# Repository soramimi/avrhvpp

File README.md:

# avrhvpp

ATmega32U2 で動作する、AVR マイコン用の +12V 高電圧パラレルプログラマ（HVPP）です。
通常は STK500 互換の ISP プログラマとして動作し、専用コマンドを送ると高電圧パラレルプログラミングモード（AVRHVPP モード）に切り替わります。

ヒューズ設定の誤りで ISP が使えなくなったチップ（SPIEN 無効、DWEN 有効など）の読み出しと復旧を主な目的としています。

ホストツールは、対応する7チップでシグネチャ、ヒューズ／ロック、Flashページ／Intel HEXの読み書きとチップ消去に対応します。ATmegaの5チップはHVPP／AVRISPに、ATtiny2313／ATtiny13AはAVRISPのみに対応します。2026-11-10、ユーザーがATmegaの5チップについてHVPP／AVRISPの全対応コマンドを実機確認し、問題がないことを報告しました。当時のAVRISP拡張の実装計画は全工程完了・クローズしています。今回追加したATtinyの2チップは実機未確認です。ホストツールとHVPPのEEPROM読み書きは未実装です。

## 対応ターゲット

Flashのページ／Intel HEX操作は`--target <name>`で次のターゲットを指定します。

| ターゲット | シグネチャ | Flash容量 | ページサイズ | ページ数 | プログラマ種別 |
|---|---|---|---|---|---|
| `atmega8` | `1E 93 07` | 8 KiB | 64バイト | 128 | HVPP／AVRISP |
| `atmega48` | `1E 92 05` | 4 KiB | 64バイト | 64 | HVPP／AVRISP |
| `atmega88` | `1E 93 0A` | 8 KiB | 64バイト | 128 | HVPP／AVRISP |
| `atmega168` | `1E 94 06` | 16 KiB | 128バイト | 128 | HVPP／AVRISP |
| `atmega328p` | `1E 95 0F` | 32 KiB | 128バイト | 256 | HVPP／AVRISP |
| `attiny2313` | `1E 91 0A` | 2 KiB | 32バイト | 64 | AVRISPのみ |
| `attiny13a` | `1E 90 07` | 1 KiB | 32バイト | 32 | AVRISPのみ |

ターゲット固有値とワードアドレス計算は`common/target.h`に集約しています。ATmega8は[データシート](https://ww1.microchip.com/downloads/en/DeviceDoc/Atmel-2486-8-bit-AVR-microcontroller-ATmega8_L_datasheet.pdf)のParallel Programming（218～225ページ）でピン配置、モード移行、アドレス指定、ページロード／書き込み手順を確認しました。

ATmega48／88／168は[データシート](https://ww1.microchip.com/downloads/en/DeviceDoc/Atmel-2545-8-bit-AVR-Microcontroller-ATmega48-88-168_Datasheet.pdf)の32.2～32.7節で拡張ヒューズ、シグネチャ、ページ構成、HVPPピン配置、モード移行、Flashのアドレス指定とページロード／書き込みを確認し、定義を追加しました。3種類とも`--query`で拡張ヒューズを表示します。P／PA／PBなど異なるシグネチャの品種は今回追加していません。3種類ともHVPP／AVRISPの全対応コマンドをユーザーが実機確認済みです。データシートのモード移行手順にはVCCの切り替えが含まれますが、常時給電の現回路での動作確認で問題は報告されていません。ファームウェアのモード移行処理は変更していません。

ATtiny2313は[データシート](https://ww1.microchip.com/downloads/en/DeviceDoc/Atmel-2543-AVR-ATtiny2313_Datasheet.pdf)の158～160、172～175ページ、ATtiny13Aは[データシート](https://ww1.microchip.com/downloads/aemDocuments/documents/MCU08/ProductDocuments/DataSheets/ATtiny13A-Data-Sheet-DS40002307A.pdf)の17.1～17.6節で、シグネチャ、Flashページ構成、ヒューズ／ロック、ISP命令と完了待ちを確認しました。STK500の標準設定値は[avrdude v8.1のターゲット定義](https://github.com/avrdudes/avrdude/blob/v8.1/src/avrdude.conf.in)も参照しています。両チップとも書き込み・消去後はRDY/BSYをポーリングします。ATtiny2313には拡張ヒューズがありますが、ATtiny13Aにはありません。ATtiny13Aのhigh fuseは下位5ビットが有効で、SPIENはlow fuseのbit 7です。両チップのロックビットは下位2ビットです。

ATtinyの2チップは`--device avrisp`を指定し、ISPヘッダJ2へ接続して使用します。本プロジェクトではHVPPに対応せず、既定のHVPPまたは`--device hvpp`と組み合わせたターゲット指定は、読み出しを含む全操作で接続前に拒否します。ターゲット未指定のHVPPの`--query`で検出した場合も、ヒューズ／ロックは読み出さず失敗します。ATtiny2313Aなど他品種の定義は追加していません。

未知の名前と複数回のターゲット指定は接続前に拒否します。Flash操作では指定が必須です。ヒューズなどの操作での指定必須化、指定ターゲットとのシグネチャ照合、既存HVPP操作へのヒューズ等の対応機能による実行可否判定は未実装です。

2026-11-10、既存5チップ（ATmega8／48／88／168／328P）、HVPP／AVRISP、全対応コマンドで問題がないことをユーザーが確認しました。自動テストと実機確認を含む当時のステップ1～8は完了し、実装計画をクローズしました。

最終ビルド記録はFlash 9422 / 32768バイト（28.8%）、RAM 676 / 1024バイト（66.0%）です。

## ディレクトリ構成

| パス | 内容 |
|---|---|
| `firmware-atmega32u2/` | プログラマ本体（ATmega32U2）のファームウェア |
| `app/` | ホスト用コマンドラインツール（`avrhvpp`） |
| `common/` | 共有するコマンド／プロトコル定義と、ホスト用のターゲット定義 |
| `pcb/` | KiCad の回路図・基板データ、ガーバー |

## ハードウェア

- MCU: ATmega32U2（16MHz クリスタル、USB CDC で接続）
- ターゲット: 28 ピン ZIF ソケット（ATmega328P／ATmega8で読み書き確認済み）
- +12V: MT3608 昇圧モジュール（J4 経由）→ 12V レギュレータ（U3）で生成し、PC817 フォトカプラでターゲットの RESET に印加します。印加しないときは R6 により RESET が GND に落ちるので、ソケットのチップはリセット状態で停止しています。
- ターゲットの VCC は常時供給されます（VCC の切り替え回路はありません）。

### ピン割り当て（ATmega32U2 ↔ ターゲット）

| ATmega32U2 | 信号 | ターゲット（ATmega328P DIP28） |
|---|---|---|
| PD0–PD7 | DATA0–7 | PB0–PB5（14–19 番）、PC0–PC1（23、24 番） |
| PB3 | RDY/BSY | PD1（3 番） |
| PB4 | PAGEL | PD7（13 番） |
| PB5 | XA1 | PD6（12 番） |
| PB6 | XA0 | PD5（11 番） |
| PB7 | XTAL1 | XTAL1（9 番） |
| PC2 | +12V 制御（PC817） | RESET（1 番） |
| PC4 | OE | PD2（4 番） |
| PC5 | WR | PD3（5 番） |
| PC6 | BS1 | PD4（6 番） |
| PC7 | BS2 | PC2（25 番） |

STK500 モードでは PB0（RST）、PB1（SCK）、PB2（MOSI）、PB3（MISO）を ISP 用に使い、6 ピンヘッダ J2 に出しています。PB3 は RDY/BSY と共用です。
J3 をショートすると J2 の RST が ATmega32U2 自身の RESET につながり、外部のプログラマから ATmega32U2 にファームウェアを書き込めます。

## ビルドと書き込み

### ファームウェア

avr-gcc と avrdude が必要です。

```sh
cd firmware-atmega32u2
make            # avrhvpp.hex を生成
make write      # 外部 ISP プログラマ（avrisp, /dev/ttyACM0）で書き込み（ヒューズ hfuse=0xD9, lfuse=0x5E も設定）
make readfuse   # ATmega32U2 のヒューズを読み出し
```

`Makefile` はコンパイル時に `.d` ファイルを生成し、ヘッダの依存関係を追跡します。

### ホストツール

C++17 のコンパイラが必要です。Qt Creator で `app/avrisp.pro` を開くか、次のようにビルドします。

```sh
cd app
g++ -std=c++17 -Wall -Wextra main.cpp serial.cpp -o avrhvpp
```

## 自動確認と確認状況

リポジトリのルートで実行します。実機へのアクセスやavrdudeの起動は行いません。

```sh
make -C tests
```

| テスト | 検証する内容 |
|---|---|
| `tests/protocol.cpp` | 実際のホスト処理とHVPPファームウェアを模擬GPIOで接続。AVRISPはシリアル・ターゲットモデルで分割送受信、7チップの読み書き・消去・HEX、事前確認、異常応答・期限切れ・終了処理を検証。ATtinyのHVPP指定拒否、ヒューズ構成とSPIEN保護も確認 |
| `tests/stk500.cpp` | 変更していないファームウェアの`main.cpp`を使用し、USBバッファ・STK500解析・SPI処理を検証。7チップの標準設定、シグネチャ、ヒューズ／ロック、ページ転送、消去後再初期化、終了、モード切り替えを確認 |

STK500の要求列は[avrdude v8.1の実装](https://github.com/avrdudes/avrdude/blob/v8.1/src/stk500.c)とAVR061に基づいて構成した固定データです。実機で採取した通信ログではありません。USB入力を1／7／16バイトに分割し、ページ境界・最終ページ、最大256バイト転送とデータ中の制御値も確認します。

異常系テストでは想定したエラーメッセージを出力します。終了コード0と、`Protocol integration and boundary tests passed without hardware.`および`STK500v1 firmware compatibility fixtures passed without hardware.`の合格表示を確認してください。

サニタイザ付きで両テストを実行する場合は次を使います（LeakSanitizerは実行環境の制約により無効化）。

```sh
ASAN_OPTIONS=detect_leaks=0 make -C tests CXXFLAGS='-std=c++17 -Wall -Wextra -fsanitize=address,undefined -fno-omit-frame-pointer' TEST_BINARY=/tmp/avrhvpp-sanitized
```

AVRISP拡張によるファームウェアの動作変更はありません（Copyright表記のみ2026へ更新）。ATtinyの追加でもファームウェアは変更していません。自動確認では実際のUSBコントローラ、SPIの電気信号、実時間のタイミング、実際のavrdudeプロセスと実機の組み合わせまでは検証しません。実機確認は別途ユーザーが実施し、2026-11-10にATmegaの5チップ・HVPP／AVRISP・全対応コマンドで問題なしと報告しました。ATtiny2313／ATtiny13Aの実機確認は未実施です。

## 使い方

### STK500 互換モード（ISP）

電源投入時はこのモードです。ArduinoISP 由来の STK500v1 実装なので、avrdude からは `avrisp` として使えます。

```sh
avrdude -c avrisp -P /dev/ttyACM0 -b 19200 -p atmega328p -U flash:w:foo.hex
```

### ホストツール（HVPP／AVRISP）

ホストのプログラマ種別は`-d <device>` / `--device <device>`で指定します。既定の`hvpp`では従来のHVPP操作を使用できます。`avrisp`ではSTK500v1経由のシグネチャ、`--query`（`-q`）、ヒューズ／ロック、Flashページ／HEXの読み出しに対応します。ヒューズ／ロック書き込み、チップ消去、Flashページ書き込みにも対応します。AVRISPの`--write-hex`にも対応します。

```sh
./avrhvpp --port /dev/ttyACM0 --device avrisp --read-signature
./avrhvpp --port /dev/ttyACM0 --device avrisp -q
./avrhvpp --port /dev/ttyACM0 --device avrisp -rfl -rfh -rl
./avrhvpp --port /dev/ttyACM0 --device avrisp --target atmega328p --read-page 255 page.bin
./avrhvpp --port /dev/ttyACM0 --device avrisp --target atmega8 --read-hex flash.hex
./avrhvpp --port /dev/ttyACM0 --device avrisp --target atmega328p --write-hex firmware.hex
./avrhvpp --port /dev/ttyACM0 --device avrisp --target atmega328p --write-hex firmware.hex --no-chip-erase
./avrhvpp --port /dev/ttyACM0 --device avrisp --target attiny2313 -q
./avrhvpp --port /dev/ttyACM0 --device avrisp --target attiny13a --write-hex firmware.hex
```

AVRISPの送受信は分割されても全バイトが揃うまで処理し、応答の`STK_INSYNC`と`STK_OK`を検証します。同期は最大3回試し、各応答は1秒の期限で読み取ります。複数の読み出し操作は1回のプログラミングセッションで順に処理し、全読み取りと終了処理が成功してから成功結果を表示します。`--target`を指定した場合は、ターゲット定義から生成した標準のSET_DEVICE／SET_DEVICE_EXT設定をモード移行前に送信します。指定ターゲットとのシグネチャ自動照合は行いません。

`--query`は`--target`不要で、HVPPと同じ形式でチップ情報と対応するヒューズ／ロックを表示します。単独のヒューズ／ロック読み出しでは、指定ターゲット、またはシグネチャから検索した定義を使います。未知のシグネチャでは検索に失敗し、ヒューズ／ロックを読みません。ATmega8の拡張ヒューズは`--query`で省略し、単独の`-rfe`指定は拒否します。ページ／HEX読み出しは`--target`必須です。ページ全体／Flash全体の読み出し成功後にファイルを保存するため、通信途中の失敗では対象ファイルを作成・上書きしません。保存後に終了処理が失敗した場合は、保存済みファイルを残して非0で終了します。

AVRISPの`--write-page`は`--target`必須で、入力サイズとページ番号を接続前に検証します。内容が一致するページは書き込みを省略し、全バイトFFのページだけを書き込み、それ以外は消去せず拒否します。書き込み後はページ全体を読み戻して照合します。`--chip-erase`は完了待ち後にロックビット解除と全FlashのFFを確認します。EEPROMの消去・保持はターゲットのEESAVE設定に従います。

ページ／HEXのファイル処理とページ走査はHVPP／AVRISPで共通です。`--write-hex`は接続前にHEX全体を検証し、既定でチップを消去してから、HEXで指定されたページだけを書き込みます。`--no-chip-erase`では全対象ページが空か一致することを先に確認し、競合や読み出し失敗があれば1ページも書きません。一致ページは省略し、HEXに含まれないページは書き込みません。`--device`、`--target`、`--no-chip-erase`の記述位置によらず、操作は左から順に実行します。

ヒューズ／ロック書き込みと消去では、指定ターゲットがなければ、最初に独立した読み出しセッションでシグネチャから定義を検索します。定義を確定して標準設定を送り直してから、指定操作を順に実行します。未知のシグネチャには書き込み・消去を送りません。ATmega8は書き込み後10 ms／消去後20 ms待機し、他6チップはRDY/BSYのbit 0を最大100 msポーリングします。STK500のACKだけでは成功と判定しません。

予約ビットは1へ正規化し、有効ビットで読み戻しを照合します。SPIENの変更と、消去なしのロックビット0→1変更は拒否します。ATmega8／ATtiny13Aの拡張ヒューズ読み書きも拒否します。失敗後の操作は停止し、非0で終了します。それまでに照合済みの書き込み・消去は失敗時も表示し、取り消しません。失敗した要求は再送しません。単独ページ書き込みで自動消去は行いません。

モード移行を試みた後は、要求の境界を確認できる場合に終了コマンドを送り、終了処理は一度だけ再試行します。2バイトの同期・モード開始・シグネチャ読出し・終了要求は、送信済み位置から残りを補って終了を試みます。可変長要求の途中送信失敗では、残りを埋めたり要求を再送したりせず接続を閉じ、プログラミングモードの解除を確認できないことを報告します。

不明なプログラマ種別、種別の重複指定、AVRISPで未対応の操作は接続前に拒否します。`--device`の位置にかかわらず、全操作の検証が済んでから接続します。

```sh
./avrhvpp -p /dev/ttyACM0 --read-signature      # シグネチャを読み出し
./avrhvpp -p /dev/ttyACM0 --query              # チップを検出し、対応するヒューズとロックビットを表示
./avrhvpp -p /dev/ttyACM0 --read-fuse-low       # low fuse を読み出し
./avrhvpp -p /dev/ttyACM0 --read-fuse-high      # high fuse を読み出し
./avrhvpp -p /dev/ttyACM0 --read-fuse-extended  # extended fuse を読み出し
./avrhvpp -p /dev/ttyACM0 --read-lock           # ロックビットを読み出し
./avrhvpp -p /dev/ttyACM0 --target atmega328p --read-page 0 page.bin # Flashのページ0を128バイトのファイルへ保存
./avrhvpp -p /dev/ttyACM0 --target atmega328p --read-hex flash.hex   # Flash全体をIntel HEXへ保存
./avrhvpp -p /dev/ttyACM0 --target atmega328p --write-page 0 page.bin # 128バイトのファイルをFlashのページ0へ書き込む
./avrhvpp -p /dev/ttyACM0 --target atmega328p --write-hex example/blink.hex # Intel HEXをFlashへ書き込む
./avrhvpp -p /dev/ttyACM0 --target atmega328p --no-chip-erase --write-hex example/blink.hex # チップ消去せずに書き込む
./avrhvpp -p /dev/ttyACM0 --write-fuse-low 0x62 # low fuse に 0x62 を書き込む
./avrhvpp -p /dev/ttyACM0 --write-lock 0xFC     # ロックビットに 0xFC を書き込む
./avrhvpp -p /dev/ttyACM0 --chip-erase          # Flash、EEPROM、ロックビットを消去
./avrhvpp -p /dev/ttyACM0 --dump-buffer         # 共有バッファを16進ダンプする（デバッグ用）
```

ヒューズ値を誤るとISPでアクセスできなくなることがあります。ロックビットは0のビットがプログラムされ、1へ戻すにはチップ消去が必要です。チップ消去はFlashとロックビットに加え、EESAVE fuseがプログラムされていなければEEPROMも消去します。Flashページ書き込みは、ページが消去済み（全バイト `0xFF`）か、すでに入力データと完全一致する場合だけ成功します。`--write-hex` は既定で書き込み前にチップ消去します。消去したくない場合は `--no-chip-erase` を指定してください。書き込む値と対象チップを確認してから実行してください。

シグネチャの出力例:

```
0x1e, 0x95, 0x0f
```

`--query`（省略形`-q`）は`--target`を指定せずに実行できます。シグネチャ3バイトから定義済みターゲットを検索し、チップ名、ページサイズ、総ページ数、Flashサイズと、対応するヒューズ／ロックビットを表示します。ATmega328Pの場合の出力例:

```text
signature: 0x1e, 0x95, 0x0f
chip: ATmega328P
page size: 128 bytes
page count: 256
flash size: 32768 bytes
fuse lo: 0x62
fuse hi: 0xd9
fuse ex: 0xff
lock bits: 0xfc
```

上記のヒューズ／ロック値は例です。ATmega8では拡張ヒューズを読み出さず、その行も表示しません。未定義のシグネチャでは`chip: unknown`を表示し、ヒューズ／ロックを読まず非0で終了します。取得失敗や異常応答でも後続操作を停止します。検出結果は後続のFlash操作の`--target`指定を変更しません。

オプション:

| オプション | 内容 |
|---|---|
| `-p <port>`, `--port <port>` | シリアルポート（Windows では `COM3` など） |
| `-d <device>`, `--device <device>` | プログラマ種別（既定`hvpp`、`avrisp`は読み出しとヒューズ／ロック／ページ／HEX書き込み・消去に対応） |
| `-t <target>`, `--target <target>` | ターゲットを選択（`atmega8`、`atmega48`、`atmega88`、`atmega168`、`atmega328p`、`attiny2313`、`attiny13a`）。Flashページ／HEX操作では必須。ATtinyの2チップは`--device avrisp`が必要 |
| `-s <speed>`, `--speed <speed>` | ボーレート（既定 115200。USB CDC なので通常は無関係） |
| `--debug` | 予約済みのデバッグコマンドを送る。ファームウェア側の処理は現在無効で、応答しない |
| `-q`, `--query` | シグネチャ、検出したチップ名、対応するヒューズとロックビットを表示する。`--target`不要 |
| `-rs`, `--read-signature` | シグネチャ3バイトを読み出す |
| `-rfl`, `--read-fuse-low` | low fuseを読み出す |
| `-rfh`, `--read-fuse-high` | high fuseを読み出す |
| `-rfe`, `--read-fuse-extended` | extended fuseを読み出す |
| `-rl`, `--read-lock` | ロックビットを読み出す |
| `--read-page <page> <file>` | 選択ターゲットのFlashページをバイナリファイルへ保存する |
| `--read-hex <file>` | 選択ターゲットのFlash全体をIntel HEXへ保存する |
| `--write-page <page> <file>` | 選択ターゲットのページサイズと一致するバイナリファイルを指定ページへ書き込む |
| `--write-hex <file>` | Intel HEXを解析し、チップ消去後に指定されたFlashページを書き込む |
| `--no-chip-erase` | `--write-hex` 前の自動チップ消去を無効にする。引数内の位置は問わない |
| `-wfl`, `--write-fuse-low <value>` | low fuseへ1バイト書き込む |
| `-wfh`, `--write-fuse-high <value>` | high fuseへ1バイト書き込む |
| `-wfe`, `--write-fuse-extended <value>` | extended fuseへ1バイト書き込む |
| `-wl`, `--write-lock <value>` | ロックビットへ1バイト書き込む |
| `--chip-erase` | Flash、EEPROM、ロックビットを消去する。ヒューズは変更しない |
| `--dump-buffer` | 共有バッファを16バイト×16行の16進数で表示する（デバッグ用） |

コマンドの指定は必須です。書き込み値は16進数で、`0x62`または`62`のように00～FFの範囲で指定します。複数の操作を指定した場合は左から順に実行し、失敗した時点で停止します。ポートや通信速度を含む全引数を検証してから接続するため、オプションの記述順に制約はありません。

## 通信プロトコル

### モードの切り替え

| 送信 | 応答 | 動作 |
|---|---|---|
| `.AVRHVPP.` | `AVRHVPP\r\n` | AVRHVPP モードに切り替え |
| `.BITBANG.` | `BITBANG\r\n` | BITBANG モード（ISP ピンの直接操作）に切り替え |
| 0x40 未満のバイト | — | どのモードからでも STK500 モードに戻る |

0x40 未満のバイトで自動的に戻るのは、avrdude などの STK500 クライアントを、モードを意識せずにそのまま使えるようにするためです（STK500 のコマンドは `'0'` = 0x30 などから始まります）。
その代わり、AVRHVPP モードで使えるコマンドやデータは 0x40 以上に限られます。任意の値は複数の0x40以上のバイトへ符号化して送る設計です。

ホストツールは切り替えの前に `'0'` と `' '` を送り、`0x14 0x10`（STK_INSYNC、STK_OK）が返ることを確認して同期を取ります。

### AVRHVPP モードのコマンド

コマンド値は `common/commands.h` でファームウェアとホストツールの間で共有しています。

操作の成功応答は`1\r\n`、読み出しデータは大文字の16進文字列と`\r\n`、エラーは`E<2桁の16進コード>\r\n`です。旧プロトコルとの互換性はありません。ホストとファームウェアを両方更新してください。

| エラー | 内容 |
|---|---|
| `E01` | 引数、設定状態、共有バッファ長が不正 |
| `E02` | プログラミングモードへの移行失敗（メーカーコード不一致） |
| `E03` | RDY/BSYタイムアウト |
| `E04` | 書き込み後の読み戻し検証失敗 |
| `E05` | 書き込み先が消去済みでも入力データと一致してもいない |
| `E06` | 未知のコマンド |

ホストは応答解析を共通化し、エラーや不正な応答を受けた時点で後続操作を中止します。

| コマンド | 応答 | 動作 |
|---|---|---|
| `CMD_CLEAR`（0x40） | なし | 一時データ、Flash操作パラメータ、バッファアドレス、256バイトの共有バッファを初期化する |
| `CMD_DEBUG`（0x4F） | なし | 予約済み。現在は処理が無効 |
| `CMD_READ_SIGNATURE`（0x50） | 16進6文字 + `\r\n` | シグネチャ3バイトを読み出す |
| `CMD_READ_FUSE`（0x51） | 16進2文字 + `\r\n` | 共有バッファの先頭で指定したヒューズを読み出す |
| `CMD_READ_LOCK`（0x52） | 16進2文字 + `\r\n` | ロックビットを読み出す |
| `CMD_READ_PAGE`（0x53） | `1\r\n`またはエラー | 指定した開始ワードアドレスから指定バイト数を共有バッファへ読み出す |
| `CMD_CHIP_ERASE`（0x60） | `1\r\n`またはエラー | チップ消去を実行する |
| `CMD_WRITE_FUSE`（0x61） | `1\r\n`またはエラー | 共有バッファで指定したlow/high/extended fuseへ値を書き込む |
| `CMD_WRITE_LOCK`（0x62） | `1\r\n`またはエラー | 共有バッファで指定した値をロックビットへ書き込む |
| `CMD_WRITE_PAGE`（0x63） | `1\r\n`またはエラー | 指定した開始ワードアドレスへ指定バイト数をページ書き込みする |
| `CMD_ADDR0` / `CMD_ADDR1`（0x70 / 0x71） | なし | 共有バッファの読み書き位置を設定する |
| `CMD_DATA0` / `CMD_DATA1`（0x72 / 0x73） | なし | 共有バッファの現在位置へ1バイト書き込み、位置を1進める |
| `CMD_LATCH_FLASH_PARAMS`（0x7D） | `1\r\n`またはエラー | 共有バッファ先頭の4バイトからFlash操作パラメータを確定し、共有バッファをクリアする |
| `CMD_READ_16BYTES`（0x7F） | 16進32文字 + `\r\n` | 共有バッファの現在位置から16バイト読み出し、位置を16進める |
| `CMD_LOAD_7BITS`（0x80～0xFF） | なし | 下位7ビットを一時データとしてロードする |

ファームウェアのSTK500処理とAVRHVPP処理は、同じ256バイトの `flush_buffer` を共有します。AVRHVPPの操作では、最初に `CMD_CLEAR` でバッファと書き込み位置を初期化します。任意の1バイトは `CMD_LOAD_7BITS` で下位7ビットをロードした後、最上位ビットに応じて `CMD_DATA0` または `CMD_DATA1` を送ることで現在位置へ格納されます。格納後、位置は自動的に1進みます。

`CMD_READ_FUSE` の対象番号は0がlow fuse、1がhigh fuse、2がextended fuseです。ホストツールは対象番号を共有バッファの0番へ格納してから読み出しコマンドを送ります。

ヒューズ書き込みでは共有バッファの0番に対象番号、1番に値を格納してから `CMD_WRITE_FUSE` を送ります。ロックビット書き込みでは0番に値を格納してから `CMD_WRITE_LOCK` を送ります。ファームウェアは先頭から連続して設定されたバイト数とFuse番号の範囲（0～3、3はlock）を検証しますが、チップ別の対応機能は検証しません。

Flash操作では`CMD_CLEAR`後、次の4バイトを先頭から連続して格納し、`CMD_LATCH_FLASH_PARAMS`で確定します。

| バッファ位置 | 値 |
|---|---|
| 0 | 開始ワードアドレスの下位バイト |
| 1 | 開始ワードアドレスの上位バイト |
| 2 | 処理バイト数の下位バイト |
| 3 | 処理バイト数の上位バイト |

処理バイト数は2～256の偶数で、256は`00 01`です。操作範囲は16ビットのワードアドレス内に収めます。ラッチ時に共有バッファと位置が初期化されるため、ホストは成功応答を受けてから読み出しコマンドまたは書き込みデータを送ります。パラメータは1回の読み書きで消費され、`CMD_CLEAR`とモード切り替えでも無効になります。旧ページ番号コマンド0x7Eは`E06`を返します。

ファームウェアは`common/target.h`を使用せず、チップ容量、ページ境界、対応機能、完全なシグネチャを検証しません。ホストは選択ターゲットの定義から開始ワードアドレスとページサイズを送ります。`CMD_READ_PAGE`が成功したら、バッファアドレスを0に設定し、`CMD_READ_16BYTES`をページサイズに応じた回数（64バイトのページは4回、128バイトのページは8回）送って回収します。16バイトが共有バッファ内に収まらない読み出しは`E01`を返します。

`--read-hex` は `CMD_READ_PAGE`で選択ターゲットの全ページを読み出し、すべて成功した後に出力ファイルを作成します。Intel HEXは16バイトのデータレコードとEOFレコードで構成し、全バイト `0xFF` のデータレコードは省略します。省略されたアドレスは消去済みの `0xFF` として扱います。

Flashページ書き込みでは、上記のパラメータをラッチした後、指定サイズのデータを先頭から連続して格納し、`CMD_WRITE_PAGE`を送ります。ファームウェアはパラメータと受信長を検証します。現在の内容が入力と完全一致する場合は成功し、全バイト`0xFF`の場合だけ実際に書き込みます。書き込み後は指定範囲を再読出しし、完全一致した場合だけ成功を返します。

`--write-hex` はIntel HEXのチェックサム、EOF、重複データ、選択ターゲットのFlash範囲を接続前に検証します。データ、EOF、拡張セグメントアドレス、拡張リニアアドレス、開始アドレスの各レコードに対応します。検証成功後、既定ではチップ消去を実行し、HEXで指定されたページを読み出して消去を確認してから `CMD_WRITE_PAGE` で書き込みます。HEXで省略された領域は書き込み対象になりません。

`--no-chip-erase` を指定すると自動チップ消去を省略します。この場合はHEXで指定された全ページを先に読み出し、各ページが消去済みまたは入力イメージと完全一致することを確認してから、必要なページだけを書き込みます。既存内容と競合するページがあれば、1ページも書き込まず終了します。

AVRHVPPモードのシグネチャ、ヒューズ、ロックビット、Flashページの読み出し／書き込みとチップ消去は、毎回プログラミングモードに入り、処理後に抜けます。成功／エラーの状態応答は`send_result()`でプログラミングモードと+12Vを解除してから送信します。不正な引数や未知コマンドも同じ終了処理を通り、モード切り替えでも解除します。
プログラミングモードに入れたかどうかは、RDY/BSY が High になることと、シグネチャの先頭がメーカーコード 0x1E であることで判定しています。

## 制約と今後の課題

- Flash読み書きは上記7種類のターゲット定義に対応しています（ATtinyの2チップはAVRISPのみ）。別チップを追加するときは、シグネチャ、Flash容量、ページサイズ、ページ数、対応するプログラミング方式のアドレス指定と書き込み手順をデータシートで確認し、ターゲット定義として追加します。
- ページ番号はホスト内で16ビットとして扱い、通信では開始ワードアドレスと処理バイト数へ変換します。有効なページ番号、ファイルサイズ、HEXの範囲はホストが選択ターゲットの定義に基づいて検証します。
- `CMD_DEBUG`の応答は無効です。ホストツールとHVPPのEEPROM読み書きは未実装です。既存STK500のEEPROM処理は今回の拡張・検証の対象外です。
- 0x40未満でSTK500モードへ戻る仕様を維持するため、任意の8ビット値は `CMD_LOAD_7BITS` と `CMD_DATA0` / `CMD_DATA1` などを使って0x40以上のバイトへ符号化します。
- プログラミングモードへは、VCC を常時供給したまま XTAL1 を 6 回トグルし、+12V を印加する方式で入ります。RSTDISBL がプログラムされたチップでは、ターゲットのプログラムが動いたままになり、モードに入れない可能性があります。対応するには VCC の切り替え回路と、より速い +12V のスイッチが必要です。

## ライセンス

Copyright (C) 2026 S.Fuchita (@soramimi_jp)

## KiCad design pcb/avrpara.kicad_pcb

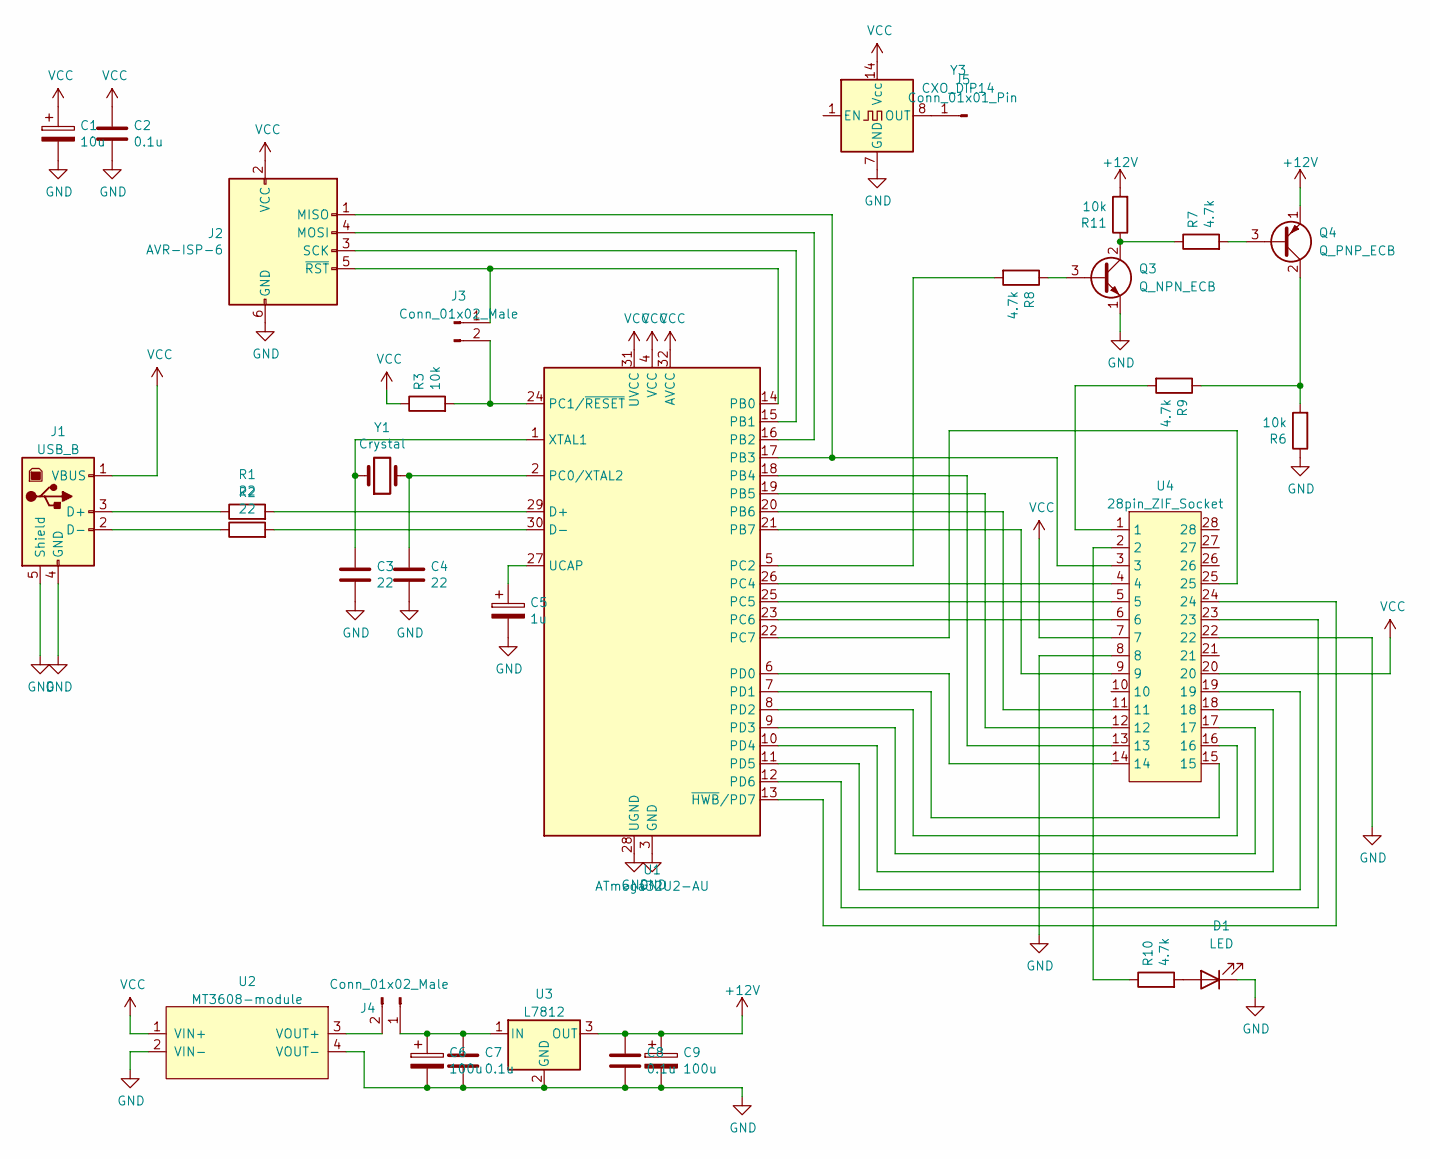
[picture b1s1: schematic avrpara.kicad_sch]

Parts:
C1: 10u; CP_Radial_D6.3mm_P2.50mm
C2, C7, C8: 0.1u; C_Disc_D3.0mm_W1.6mm_P2.50mm
C3, C4: 22; C_Disc_D3.0mm_W1.6mm_P2.50mm
C5: 1u; CP_Radial_D6.3mm_P2.50mm
C6, C9: 100u; CP_Radial_D6.3mm_P2.50mm
D1: LED; LED_D3.0mm
J1: USB_B; USB_B_Lumberg_2411_02_Horizontal
J2: AVR-ISP-6; PinHeader_2x03_P2.54mm_Vertical
J3, J4: Conn_01x02_Male; PinHeader_1x02_P2.54mm_Vertical
J5: Conn_01x01_Pin; PinHeader_1x01_P2.54mm_Vertical
Q3: Q_NPN_ECB; TO-92L_Inline_Wide
Q4: Q_PNP_ECB; TO-92L_Inline_Wide
R1, R2: 22; R_Axial_DIN0204_L3.6mm_D1.6mm_P2.54mm_Vertical
R3, R6, R11: 10k; R_Axial_DIN0204_L3.6mm_D1.6mm_P2.54mm_Vertical
R7, R8, R9: 4.7k; R_Axial_DIN0204_L3.6mm_D1.6mm_P2.54mm_Vertical
R10: 4.7k; R_Axial_DIN0207_L6.3mm_D2.5mm_P2.54mm_Vertical
U1: ATmega32U2-AU; TQFP-32_7x7mm_P0.8mm
U2: MT3608-module
U3: L7812; TO-220-3_Vertical
U4: 28pin_ZIF_Socket; ARIES 28pin ZIF Socket
Y1: Crystal; Crystal_HC49-U_Vertical
Y3: CXO_DIP14; Oscillator_DIP-14

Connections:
+12V: C8.1, C9.1, Q4.1 (E), R11.2, U3.3 (OUT)
GND: C1.2, C2.2, C3.2, C4.2, C5.2, C6.2, C7.2, C8.2, C9.2, D1.1 (K), J1.4 (GND), J1.5 (Shield), J2.6 (GND), Q3.1 (E), R6.1, U1.3 (GND), U1.28 (UGND), U2.2 (VIN-), U2.4 (VOUT-), U3.2 (GND), U4.8, U4.22, Y3.7 (GND)
unnamed: D1.2 (A), R10.2
unnamed: J1.3 (D+), R1.1
unnamed: J1.2 (D-), R2.1
unnamed: J2.1 (MISO), U1.17 (PB3), U4.3
unnamed: J2.4 (MOSI), U1.16 (PB2)
unnamed: J2.3 (SCK), U1.15 (PB1)
unnamed: J2.5 (~RST), J3.1, U1.14 (PB0)
unnamed: J3.2, R3.2, U1.24 (PC1/~RESET)
unnamed: C6.1, C7.1, J4.1, U3.1 (IN)
unnamed: J4.2, U2.3 (VOUT+)
unnamed: J5.1 (Pin_1_1), Y3.8 (OUT)
unnamed: Q3.3 (B), R8.1
unnamed: Q3.2 (C), R7.1, R11.1
unnamed: Q4.3 (B), R7.2
unnamed: Q4.2 (C), R6.2, R9.1
unnamed: R9.2, U4.1
unnamed: R10.1, U4.2
unnamed: R1.2, U1.29 (D+)
unnamed: R2.2, U1.30 (D-)
unnamed: U1.18 (PB4), U4.13
unnamed: U1.19 (PB5), U4.12
unnamed: U1.20 (PB6), U4.11
unnamed: U1.21 (PB7), U4.9
unnamed: C4.1, U1.2 (PC0/XTAL2), Y1.2
unnamed: R8.2, U1.5 (PC2)
unnamed: U1.26 (PC4), U4.4
unnamed: U1.25 (PC5), U4.5
unnamed: U1.23 (PC6), U4.6
unnamed: U1.22 (PC7), U4.25
unnamed: U1.6 (PD0), U4.14
unnamed: U1.7 (PD1), U4.15
unnamed: U1.8 (PD2), U4.16
unnamed: U1.9 (PD3), U4.17
unnamed: U1.10 (PD4), U4.18
unnamed: U1.11 (PD5), U4.19
unnamed: U1.12 (PD6), U4.23
unnamed: C5.1, U1.27 (UCAP)
unnamed: C3.1, U1.1 (XTAL1), Y1.1
unnamed: U1.13 (~HWB/PD7), U4.24
VCC: C1.1, C2.1, J1.1 (VBUS), J2.2 (VCC), R3.1, U1.4 (VCC), U1.31 (UVCC), U1.32 (AVCC), U2.1 (VIN+), U4.7, U4.20, Y3.14 (Vcc)

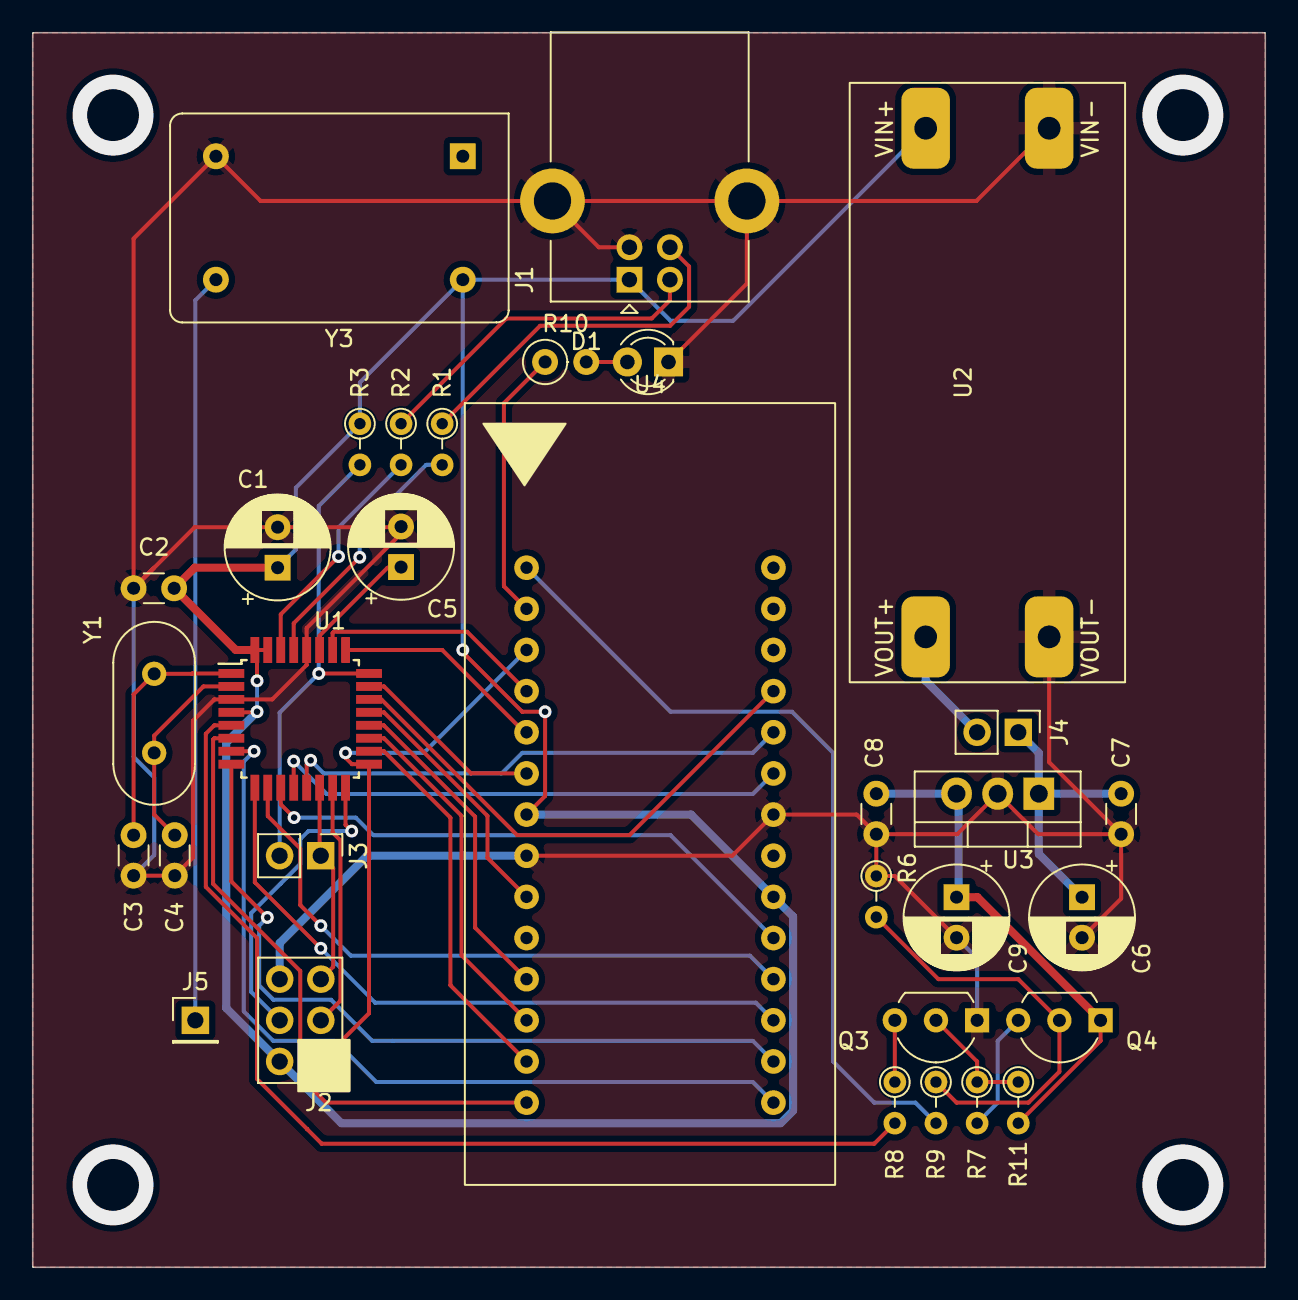
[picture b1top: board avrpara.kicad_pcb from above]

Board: 2 copper layers, 76.1 x 76.2 mm, 32 parts (0 on the bottom side), 42 nets.
